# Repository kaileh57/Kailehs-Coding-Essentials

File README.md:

# Kailehs Coding Essentials
My inspiration to make this was to learn the process of creating a macropad to move on to a more complex project, such as a keyboard. I've also wanted one of those StackOverflow copy paste keyboards FOREVER, but have never really had a chance to get one. The macropad will likely end up with a variety of configs based on the app, and should make it easier to perform common tasks as I do more development!!

Note: The enclosure is transparent; I just didn't know how to model that in CAD. If all that can be printed is opaque, that's fine. I can probably get a second case sourced at some point in the future, one I have a working prototype. 

# BOM:
- 3x Cherry MX Switches
- 2x SK6812 MINI Leds
- 1x XIAO RP2040
- 3x Blank DSA Keycaps
- 4x M3x16 Bolt
- 4x M3 Heatset
- 3d printed case

Other bits:
- KMK firmware
- Top.step
- Bottom.step

Finished assembly:

PCB schematic:

PCB layout:

PCB:

Case parts:

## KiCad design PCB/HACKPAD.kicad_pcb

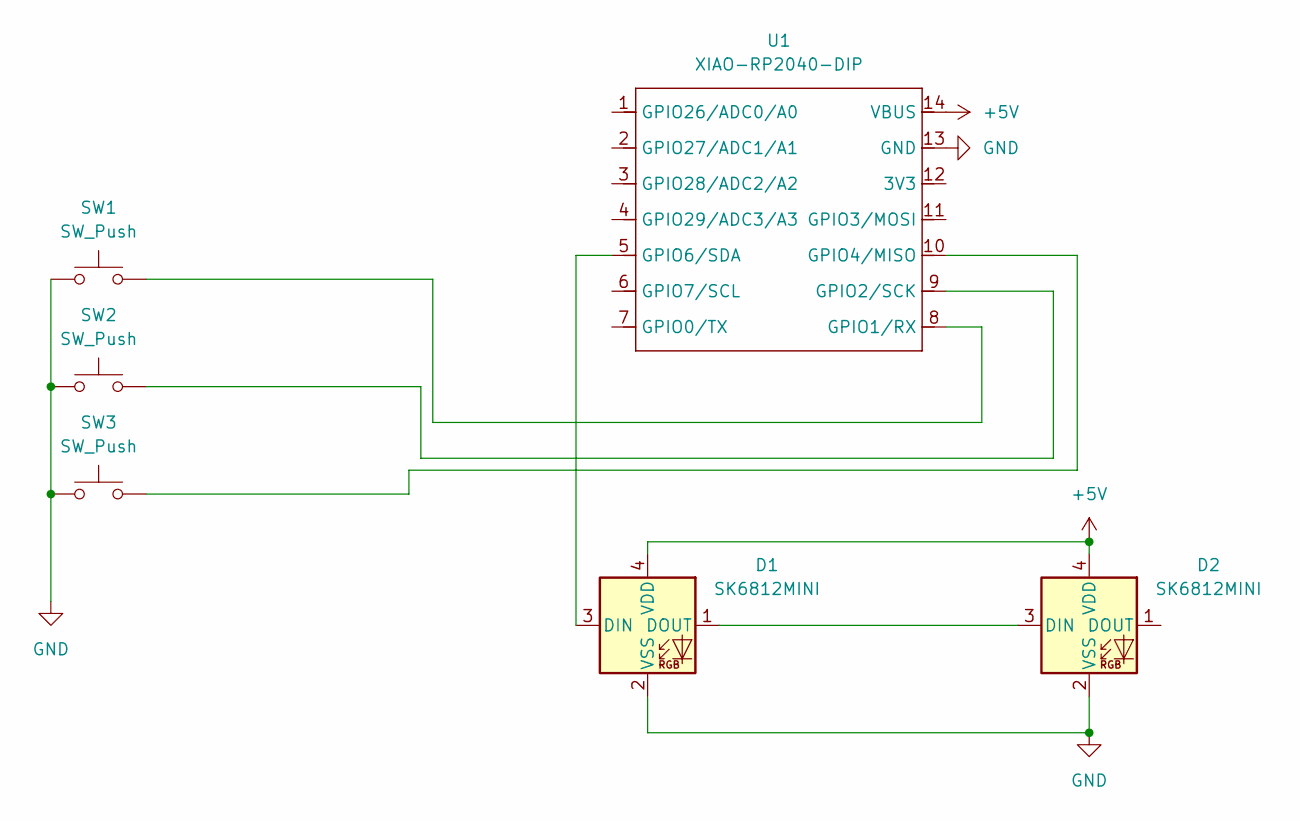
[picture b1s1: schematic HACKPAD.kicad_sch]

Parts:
D1, D2: SK6812MINI; LED_SK6812MINI_PLCC4_3.5x3.5mm_P1.75mm
SW1, SW2, SW3: SW_Push; SW_Cherry_MX_1.00u_PCB
U1: XIAO-RP2040-DIP

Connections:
+5V: D1.4 (VDD), D2.4 (VDD), U1.14 (VBUS)
GND: D1.2 (VSS), D2.2 (VSS), SW1.1, SW2.1, SW3.1, U1.13 (GND)
unnamed: D1.3 (DIN), U1.5 (GPIO6/SDA)
unnamed: D1.1 (DOUT), D2.3 (DIN)
unnamed: SW1.2, U1.8 (GPIO1/RX)
unnamed: SW2.2, U1.9 (GPIO2/SCK)
unnamed: SW3.2, U1.10 (GPIO4/MISO)

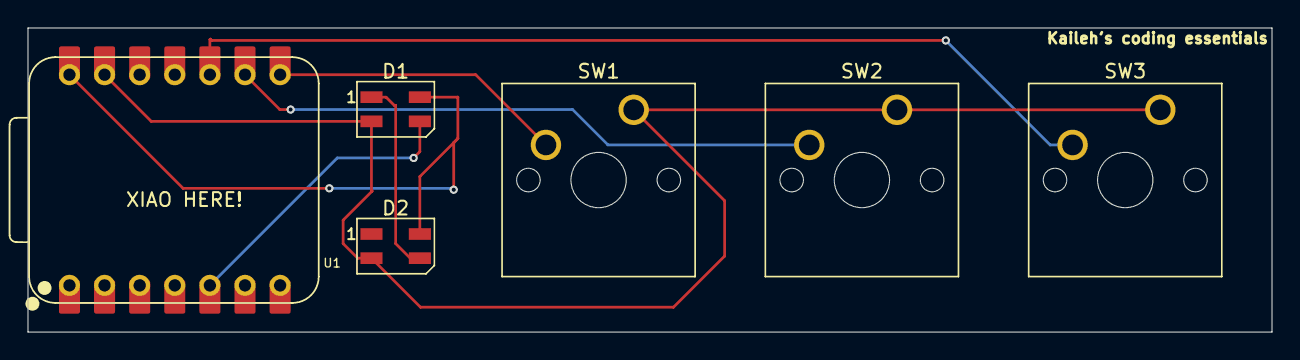
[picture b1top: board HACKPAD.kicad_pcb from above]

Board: 2 copper layers, 90.0 x 22.0 mm, 6 parts (0 on the bottom side), 7 nets.

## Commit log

2025-06-09 filesssssssssssss
2025-06-28 fix drilling
